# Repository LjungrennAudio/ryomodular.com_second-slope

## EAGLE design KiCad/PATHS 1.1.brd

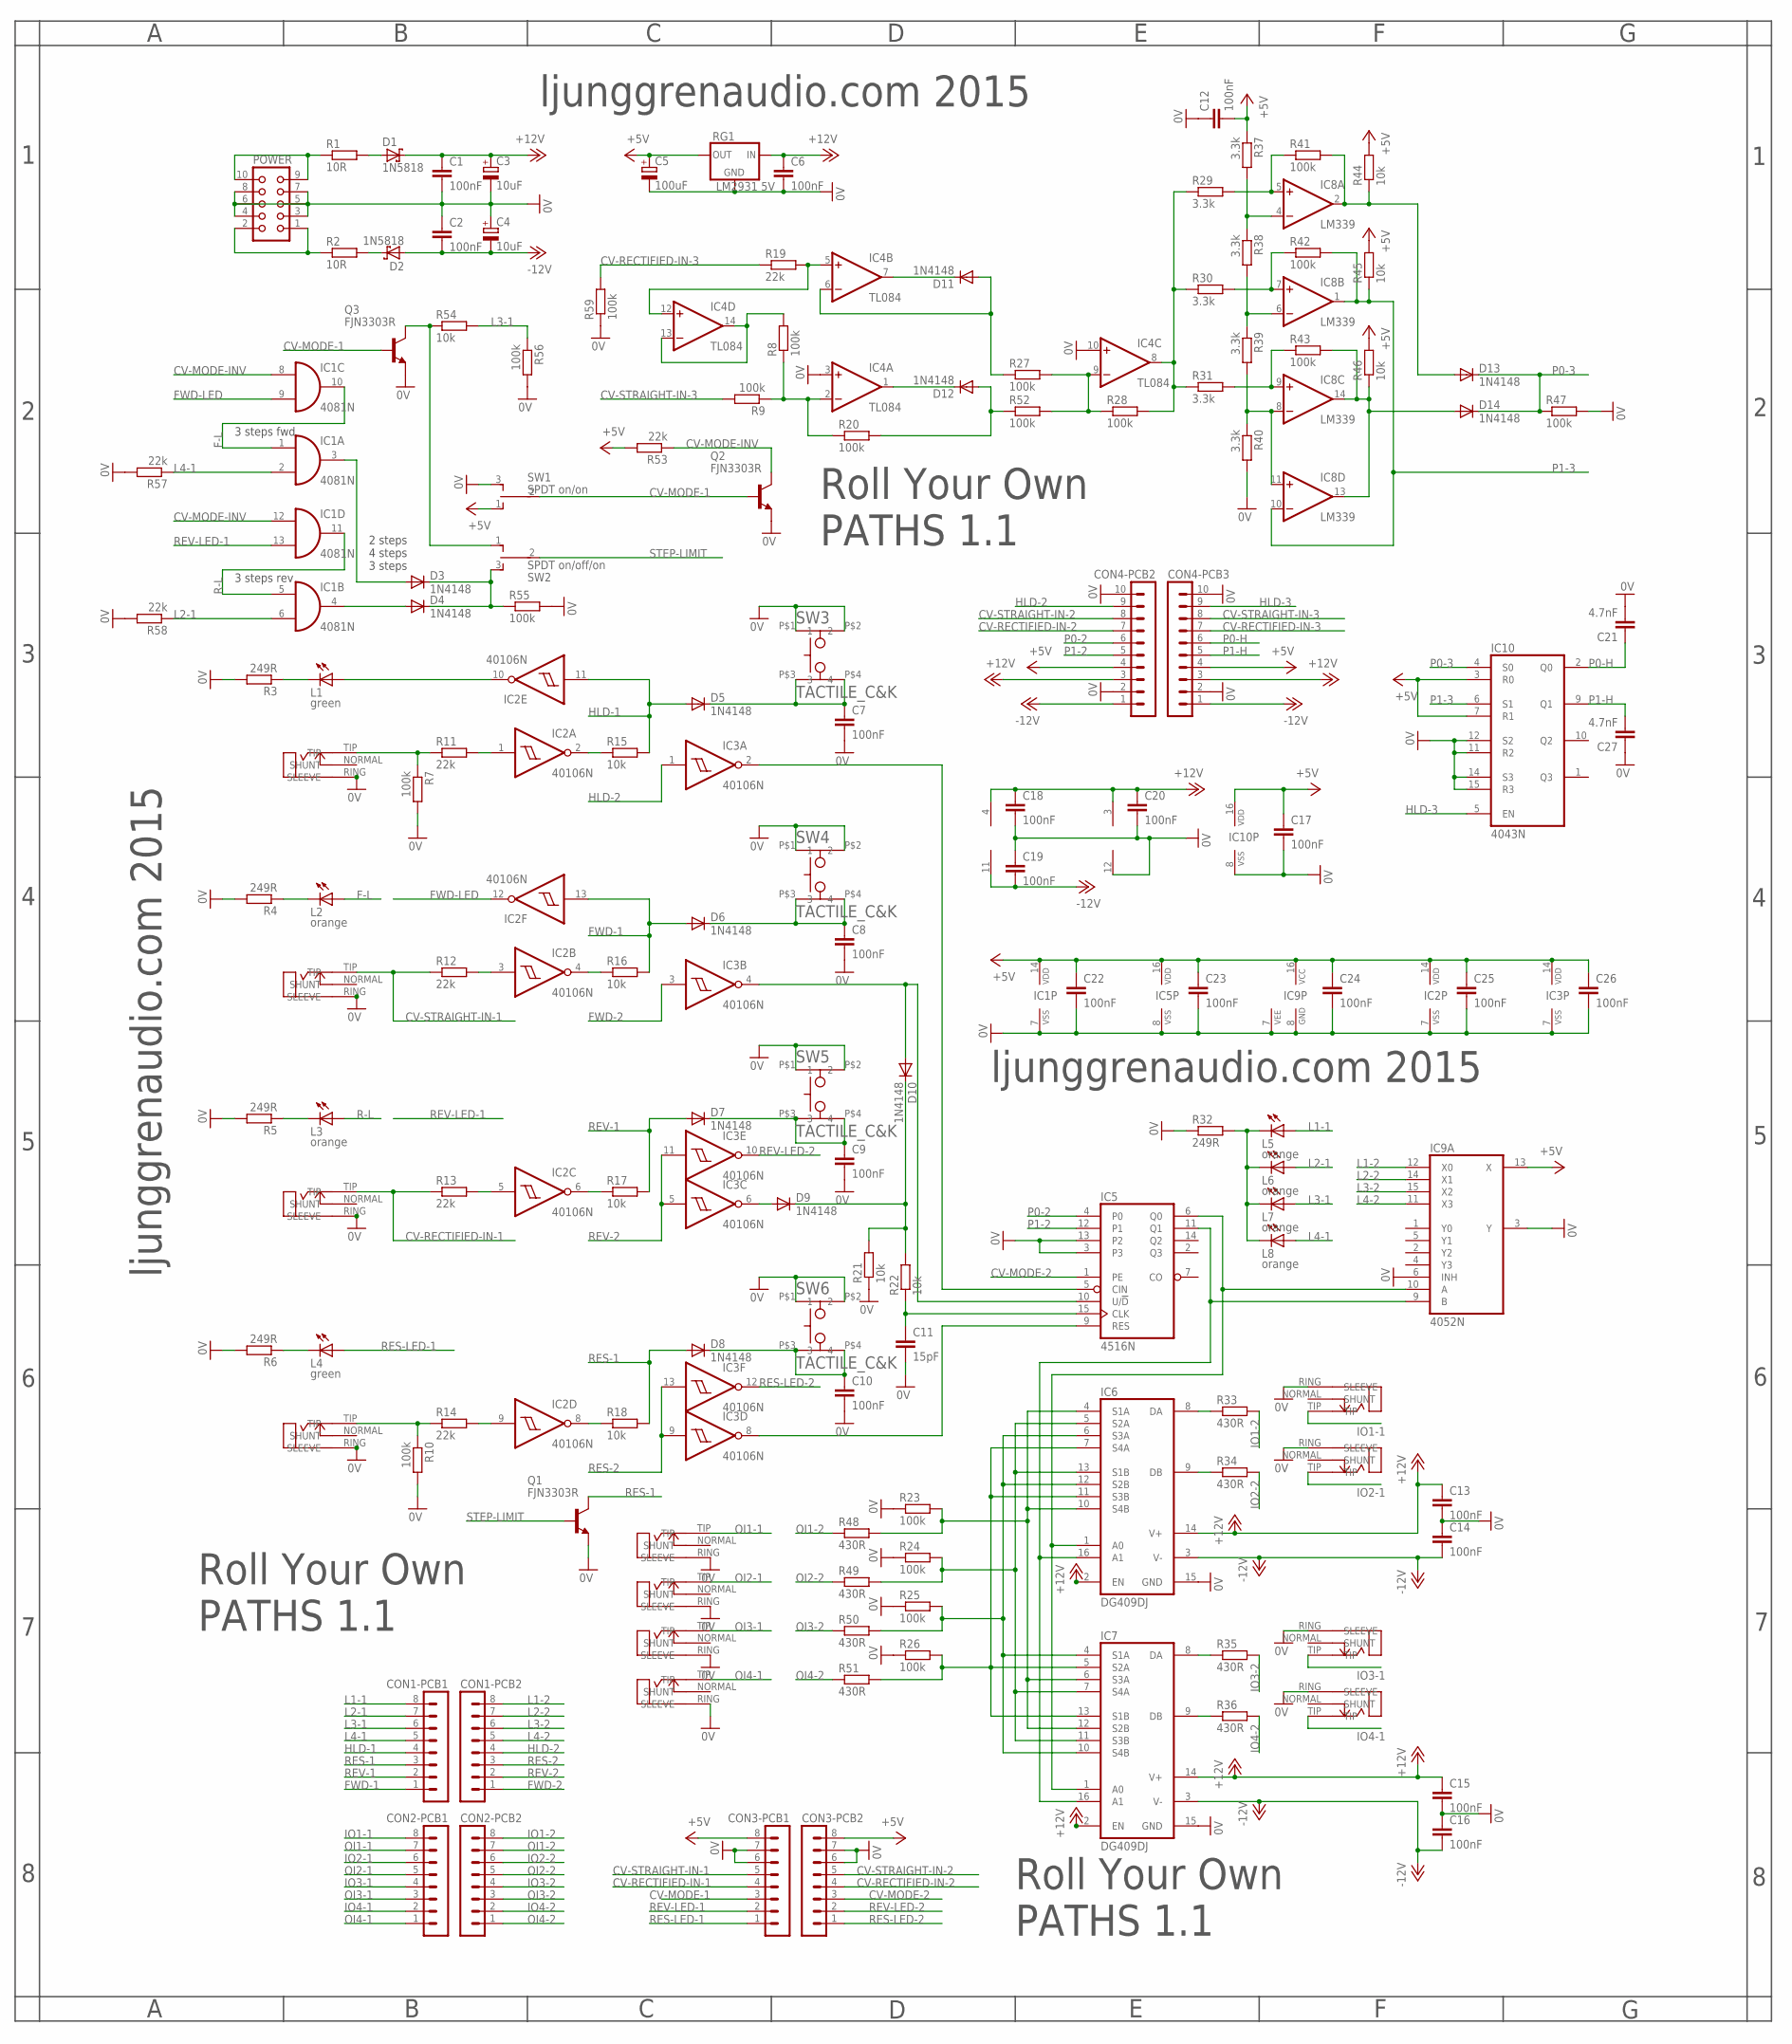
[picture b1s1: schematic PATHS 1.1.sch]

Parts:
C1, C2, C6, C7, C8, C9, C10, C12, C13, C14, C15, C16, C17, C18, C19, C20, C22, C23, C24, C25, C26: 100nF; C025-024X044
C3, C4: 10uF; E2-5
C5: 100uF; E2,5-6
C11: 15pF; C025-024X044
C21, C27: 4.7nF; C025-024X044
CON1-PCB1, CON1-PCB2, CON2-PCB1, CON2-PCB2, CON3-PCB1, CON3-PCB2: MA08-1
CON4-PCB2, CON4-PCB3: MA10-1
D1, D2: 1N5818; DO41-7
D3, D4, D5, D6, D7, D8, D9, D10, D11, D12, D13, D14: 1N4148; DO35-6
FWD: ERTHENVAR_3.5MM_JACKINLINE2; THONKICON-TWISTED
HLD: ERTHENVAR_3.5MM_JACKINLINE2; THONKICON-TWISTED
I/O1, I/O2, I/O3, I/O4: ERTHENVAR_3.5MM_JACKINLINE2; THONKICON-TWISTED
IC1: 4081N; DIL14
IC2, IC3: 40106N; DIL14
IC4: TL084; DIL14
IC5: 4516N; DIL16
IC6, IC7: DG409DJ; DIL16
IC8: LM339; DIL14
IC9: 4052N; DIL16
IC10: 4043N; DIL16
L1, L4: green; LED3MM
L2, L3, L5, L6, L7, L8: orange; LED3MM
O/I1, O/I2, O/I3, O/I4: ERTHENVAR_3.5MM_JACKINLINE2; THONKICON-TWISTED
POWER: CON10L
Q1, Q2, Q3: FJN3303R; TO92-LINE
R1, R2: 10R; 0207/9
R3, R4, R5, R6, R32: 249R; 0204/5
R7, R8, R9, R10, R20, R23, R24, R25, R26, R27, R28, R41, R42, R43, R47, R52, R55, R56, R59: 100k; 0204/5
R11, R12, R13, R14, R19, R53, R57, R58: 22k; 0204/5
R15, R16, R17, R18, R21, R22, R44, R45, R46, R54: 10k; 0204/5
R29, R30, R31, R37, R38, R39, R40: 3.3k; 0204/5
R33, R34, R35, R36, R48, R49, R50, R51: 430R; 0207/9
RES: ERTHENVAR_3.5MM_JACKINLINE2; THONKICON-TWISTED
REV: ERTHENVAR_3.5MM_JACKINLINE2; THONKICON-TWISTED
RG1: LM2931 5V; TO92-LINE
SW1: SPDT on/on; SPDT-HORIZONTAL-TOP-SUBMINI-MULTICOMP
SW2: SPDT on/off/on; SPDT-HORIZONTAL-TOP-SUBMINI-MULTICOMP
SW3, SW4, SW5, SW6: TACTILE_C&K; TACTILE_CK

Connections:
0V: C1.2, C2.1, C3.-, C4.+, C5.-, C6.2, C7.2, C8.2, C9.2, C10.2, C11.2, C12.1, C13.2, C14.1, C15.2, C16.1, C17.2, C18.2, C19.1, C20.2, C21.2, C22.2, C23.2, C24.2, C25.2, C26.2, C27.1, CON3-PCB1.6, CON3-PCB1.7, CON3-PCB2.6, CON3-PCB2.7, CON4-PCB2.2, CON4-PCB2.10, CON4-PCB3.2, CON4-PCB3.10, FWD.RING (SLEEVE), HLD.RING (SLEEVE), I/O1.RING (SLEEVE), I/O2.RING (SLEEVE), I/O3.RING (SLEEVE), I/O4.RING (SLEEVE), IC1.7 (VSS), IC2.7 (VSS), IC3.7 (VSS), IC4.3 (+IN), IC4.10 (+IN), IC5.3, IC5.8 (VSS), IC5.13 (P2), IC6.15 (GND), IC7.15 (GND), IC8.12 (V-), IC9.3 (Y), IC9.6 (INH), IC9.7 (VEE), IC9.8 (GND), IC10.8 (VSS), IC10.11 (R2), IC10.12 (S2), IC10.14 (S3), IC10.15 (R3), O/I1.RING (SLEEVE), O/I2.RING (SLEEVE), O/I3.RING (SLEEVE), O/I4.RING (SLEEVE), POWER.3, POWER.4, POWER.5, POWER.6, POWER.7, POWER.8, Q1.3 (E), Q2.3 (E), Q3.3 (E), R3.2, R4.2, R5.2, R6.2, R7.2, R10.2, R21.1, R23.1, R24.1, R25.1, R26.1, R32.1, R40.2, R47.2, R55.2, R56.2, R57.2, R58.2, R59.1, RES.RING (SLEEVE), REV.RING (SLEEVE), RG1.2 (GND), SW1.3, SW3.P$1 (1), SW3.P$2 (2), SW4.P$1 (1), SW4.P$2 (2), SW5.P$1 (1), SW5.P$2 (2), SW6.P$1 (1), SW6.P$2 (2)
+5V: C5.+, C12.2, C17.1, C22.1, C23.1, C24.1, C25.1, C26.1, CON3-PCB1.8, CON3-PCB2.8, CON4-PCB2.4, CON4-PCB3.4, IC1.14 (VDD), IC2.14 (VDD), IC3.14 (VDD), IC5.16 (VDD), IC9.13 (X), IC9.16 (VCC), IC10.3 (R0), IC10.7 (R1), IC10.16 (VDD), R37.1, R44.2, R45.2, R46.2, R53.2, RG1.3 (OUT), SW1.1
+12V: C1.1, C3.+, C6.1, C13.1, C15.1, C18.1, C20.1, CON4-PCB2.3, CON4-PCB3.3, D1.C, IC4.4 (V+), IC6.2 (EN), IC6.14 (V+), IC7.2 (EN), IC7.14 (V+), IC8.3 (V+), RG1.1 (IN)
-12V: C2.2, C4.-, C14.2, C16.2, C19.2, CON4-PCB2.1, CON4-PCB3.1, D2.A, IC4.11 (V-), IC6.3 (V-), IC7.3 (V-)
BDF3R2T: C9.1, D7.CATHODE (C), SW5.P$3 (3), SW5.P$4 (4)
CV-MODE-1: CON3-PCB1.3, Q2.1 (B), Q3.1 (B), SW1.2
CV-MODE-2: CON3-PCB2.3, IC5.1 (PE)
CV-MODE-INV: IC1.8 (I0), IC1.12 (I0), Q2.2 (C), R53.1
CV-RECTIFIED-IN-1: CON3-PCB1.4, R13.1, REV.TIP
CV-RECTIFIED-IN-2: CON3-PCB2.4, CON4-PCB2.7
CV-RECTIFIED-IN-3: CON4-PCB3.7, R19.1, R59.2
CV-STRAIGHT-IN-1: CON3-PCB1.5, FWD.TIP, R12.1
CV-STRAIGHT-IN-2: CON3-PCB2.5, CON4-PCB2.8
CV-STRAIGHT-IN-3: CON4-PCB3.8, R9.2
DFGT43: C8.1, D6.CATHODE (C), SW4.P$3 (3), SW4.P$4 (4)
DVW4D: D9.ANODE (A), IC3.6 (O)
F-L: IC1.1 (I0), IC1.10 (O), L2.A
FGDFS33: IC3.2 (O), IC5.5 (CIN)
FSS44F: IC3.8 (O), IC5.9 (RES)
FWD-1: CON1-PCB1.1, D6.ANODE (A), IC2.13 (I), R16.2
FWD-2: CON1-PCB2.1, IC3.3 (I)
FWD-LED: IC1.9 (I1), IC2.12 (O)
HLD-1: CON1-PCB1.4, D5.ANODE (A), IC2.11 (I), R15.2
HLD-2: CON1-PCB2.4, CON4-PCB2.9, IC3.1 (I)
HLD-3: CON4-PCB3.9, IC10.5 (EN)
IO1-1: CON2-PCB1.8, I/O1.TIP
IO1-2: CON2-PCB2.8, R33.2
IO2-1: CON2-PCB1.6, I/O2.TIP
IO2-2: CON2-PCB2.6, R34.2
IO3-1: CON2-PCB1.4, I/O3.TIP
IO3-2: CON2-PCB2.4, R35.2
IO4-1: CON2-PCB1.2, I/O4.TIP
IO4-2: CON2-PCB2.2, R36.2
L1-1: CON1-PCB1.8, L5.A
L1-2: CON1-PCB2.8, IC9.12 (X0)
L2-1: CON1-PCB1.7, IC1.6 (I1), L6.A, R58.1
L2-2: CON1-PCB2.7, IC9.14 (X1)
L3-1: CON1-PCB1.6, L7.A, R54.2, R56.1
L3-2: CON1-PCB2.6, IC9.15 (X2)
L4-1: CON1-PCB1.5, IC1.2 (I1), L8.A, R57.1
L4-2: CON1-PCB2.5, IC9.11 (X3)
unnamed: IC5.11 (Q1), IC6.16 (A1), IC7.16 (A1), IC9.9 (B)
unnamed: IC5.6 (Q0), IC6.1 (A0), IC7.1 (A0), IC9.10 (A)
unnamed: IC2.3 (I), R12.2
unnamed: C11.1, IC5.15 (CLK), R22.1
unnamed: IC6.9 (DB), R34.1
unnamed: IC7.9 (DB), R36.1
unnamed: L2.K (C), R4.1
unnamed: HLD.TIP, R7.1, R11.1
unnamed: IC7.8 (DA), R35.1
unnamed: IC2.4 (O), R16.1
unnamed: IC2.6 (O), R17.1
unnamed: R10.1, R14.1, RES.TIP
unnamed: IC6.8 (DA), R33.1
unnamed: L1.K (C), R3.1
unnamed: L3.K (C), R5.1
unnamed: IC2.8 (O), R18.1
unnamed: C10.1, D8.CATHODE (C), SW6.P$3 (3), SW6.P$4 (4)
unnamed: IC2.10 (O), L1.A
unnamed: D3.ANODE (A), IC1.3 (O)
unnamed: L4.K (C), R6.1
unnamed: IC2.5 (I), R13.2
unnamed: POWER.1, POWER.2, R2.1
unnamed: POWER.9, POWER.10, R1.1
unnamed: D1.A, R1.2
unnamed: D2.C, R2.2
unnamed: IC2.9 (I), R14.2
unnamed: IC2.2 (O), R15.1
unnamed: C7.1, D5.CATHODE (C), SW3.P$3 (3), SW3.P$4 (4)
unnamed: IC4.2 (-IN), R8.1, R9.1, R20.1
unnamed: D4.ANODE (A), IC1.4 (O)
unnamed: IC8.4 (-IN), R37.2, R38.1
unnamed: IC8.6 (-IN), R38.2, R39.1
unnamed: IC8.8 (-IN), IC8.11 (+IN), R39.2, R40.1
unnamed: D11.ANODE (A), IC4.6 (-IN), R27.1
unnamed: IC8.9 (+IN), R31.2, R43.1
unnamed: IC8.7 (+IN), R30.2, R42.1
unnamed: IC8.5 (+IN), R29.2, R41.1
unnamed: D9.CATHODE (C), D10.CATHODE (C), R21.2, R22.2
unnamed: L5.K (C), L6.K (C), L7.K (C), L8.K (C), R32.2
unnamed: D14.ANODE (A), IC8.13 (OUT), IC8.14 (OUT), R43.2, R46.1
unnamed: IC6.6 (S3A), IC6.12 (S2B), IC7.4 (S1A), IC7.10 (S4B), R25.2, R50.2
unnamed: D13.ANODE (A), IC8.2 (OUT), R41.2, R44.1
unnamed: IC4.5 (+IN), IC4.12 (+IN), R19.2
unnamed: D11.CATHODE (C), IC4.7 (OUT)
unnamed: D3.CATHODE (C), D4.CATHODE (C), R55.1, SW2.3
unnamed: IC6.7 (S4A), IC6.11 (S3B), IC7.5 (S2A), IC7.13 (S1B), R26.2, R51.2
unnamed: IC2.1 (I), R11.2
unnamed: D12.CATHODE (C), IC4.1 (OUT)
unnamed: IC4.9 (-IN), R27.2, R28.1, R52.2
unnamed: IC4.8 (OUT), R28.2, R29.1, R30.1, R31.1
unnamed: IC6.5 (S2A), IC6.13 (S1B), IC7.7 (S4A), IC7.11 (S3B), R24.2, R49.2
unnamed: IC6.4 (S1A), IC6.10 (S4B), IC7.6 (S3A), IC7.12 (S2B), R23.2, R48.2
unnamed: IC4.13 (-IN), IC4.14 (OUT), R8.2
unnamed: D12.ANODE (A), R20.2, R52.1
unnamed: Q3.2 (C), R54.1, SW2.1
OI1-1: CON2-PCB1.7, O/I1.TIP
OI1-2: CON2-PCB2.7, R48.1
OI2-1: CON2-PCB1.5, O/I2.TIP
OI2-2: CON2-PCB2.5, R49.1
OI3-1: CON2-PCB1.3, O/I3.TIP
OI3-2: CON2-PCB2.3, R50.1
OI4-1: CON2-PCB1.1, O/I4.TIP
OI4-2: CON2-PCB2.1, R51.1
P0-2: CON4-PCB2.6, IC5.4 (P0)
P0-3: D13.CATHODE (C), D14.CATHODE (C), IC10.4 (S0), R47.1
P0-H: C21.1, CON4-PCB3.6, IC10.2 (Q0)
P1-2: CON4-PCB2.5, IC5.12 (P1)
P1-3: IC8.1 (OUT), IC8.10 (-IN), IC10.6 (S1), R42.2, R45.1
P1-H: C27.2, CON4-PCB3.5, IC10.9 (Q1)
R-L: IC1.5 (I0), IC1.11 (O), L3.A
RES-1: CON1-PCB1.3, D8.ANODE (A), Q1.2 (C), R18.2
RES-2: CON1-PCB2.3, IC3.9 (I), IC3.13 (I)
RES-LED-1: CON3-PCB1.1, L4.A
RES-LED-2: CON3-PCB2.1, IC3.12 (O)
REV-1: CON1-PCB1.2, D7.ANODE (A), R17.2
REV-2: CON1-PCB2.2, IC3.5 (I), IC3.11 (I)
REV-LED-1: CON3-PCB1.2, IC1.13 (I1)
REV-LED-2: CON3-PCB2.2, IC3.10 (O)
STEP-LIMIT: Q1.1 (B), SW2.2
XBGE4: D10.ANODE (A), IC3.4 (O), IC5.10 (U/!D)

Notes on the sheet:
2 steps 4 steps 3 steps
3 steps fwd
3 steps rev
Roll Your Own PATHS 1.1
ljunggrenaudio.com 2015

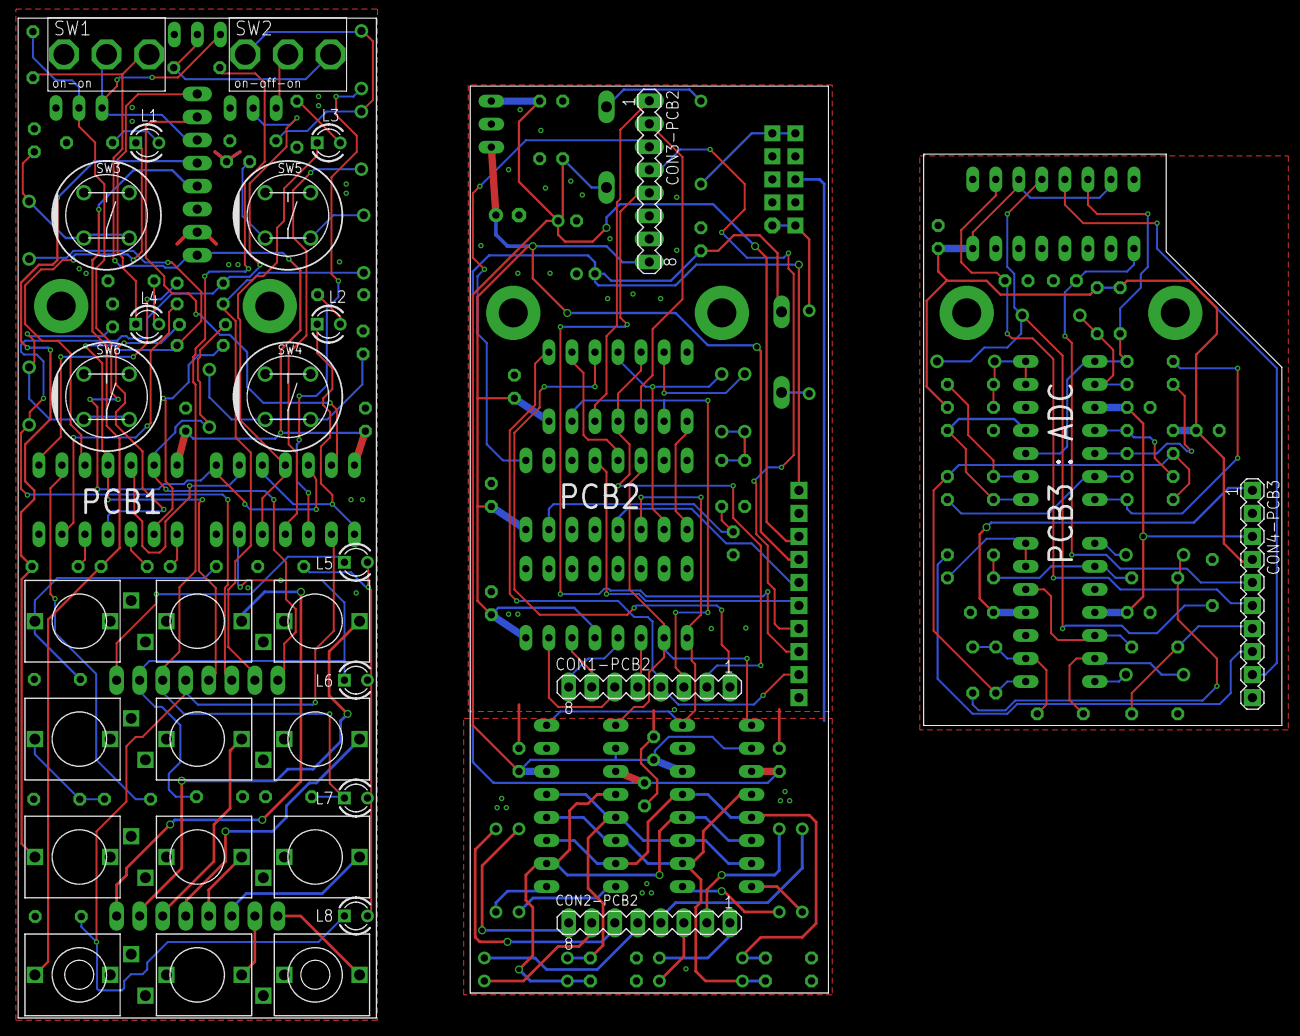
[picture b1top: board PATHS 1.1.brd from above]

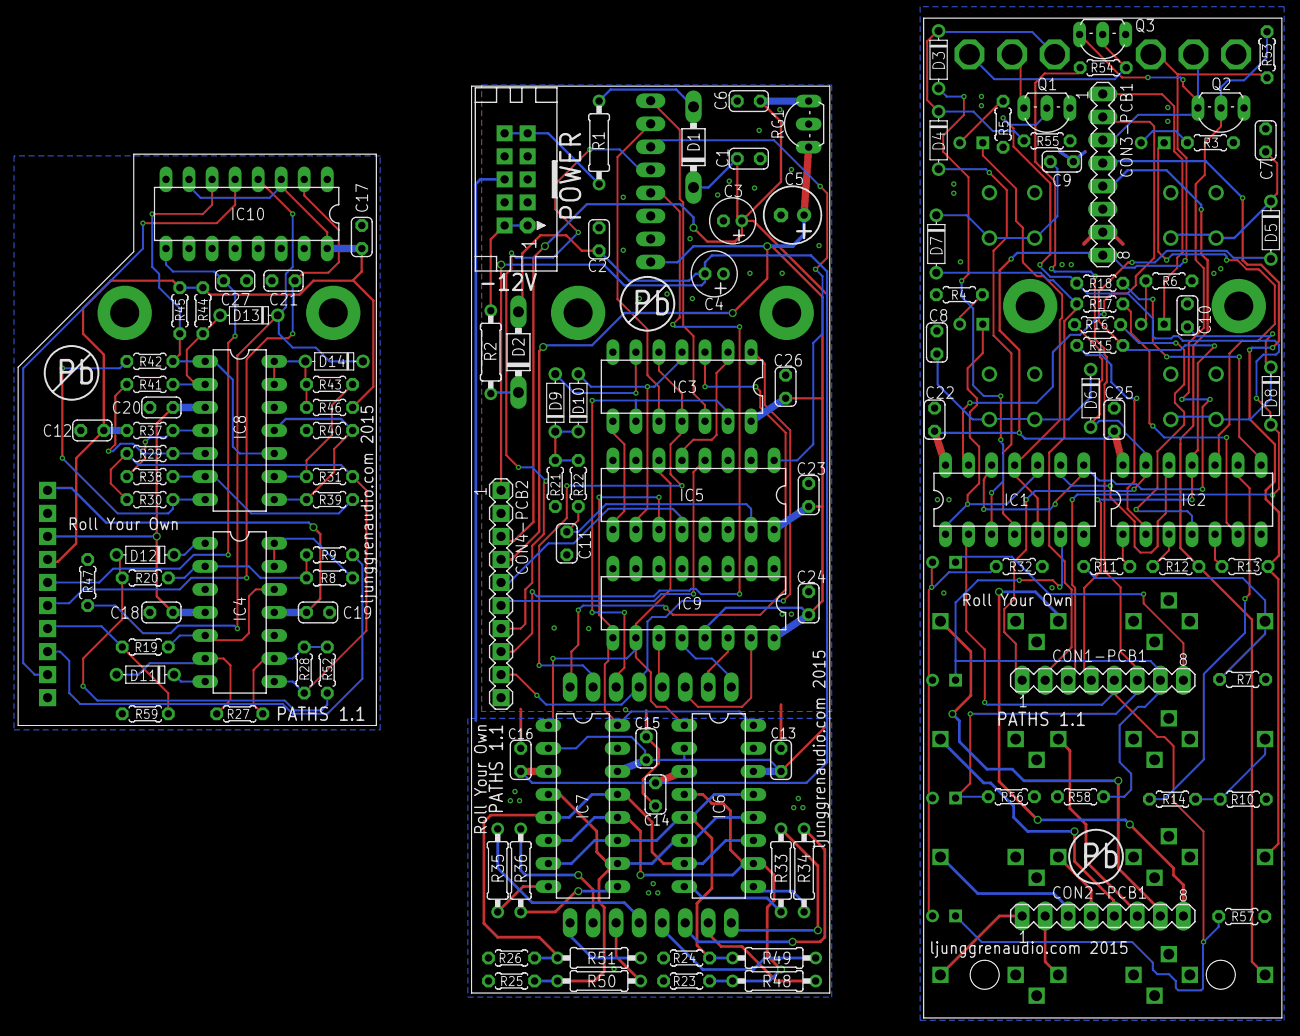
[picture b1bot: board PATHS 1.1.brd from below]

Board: 2 copper layers, 139.3 x 110.2 mm, 149 parts (119 on the bottom side), 121 nets.

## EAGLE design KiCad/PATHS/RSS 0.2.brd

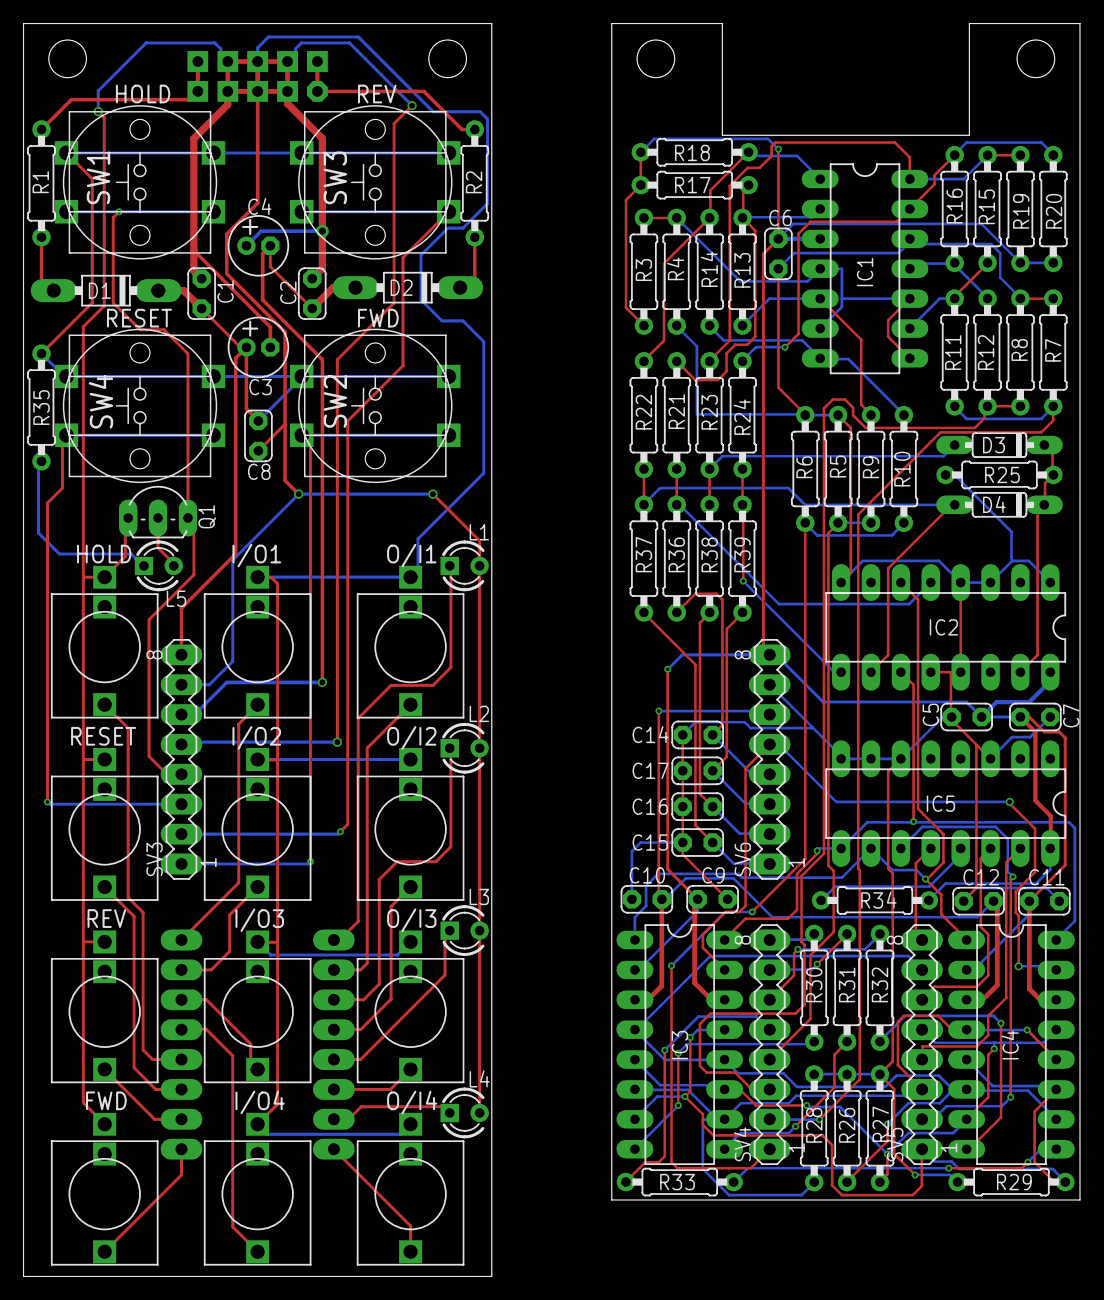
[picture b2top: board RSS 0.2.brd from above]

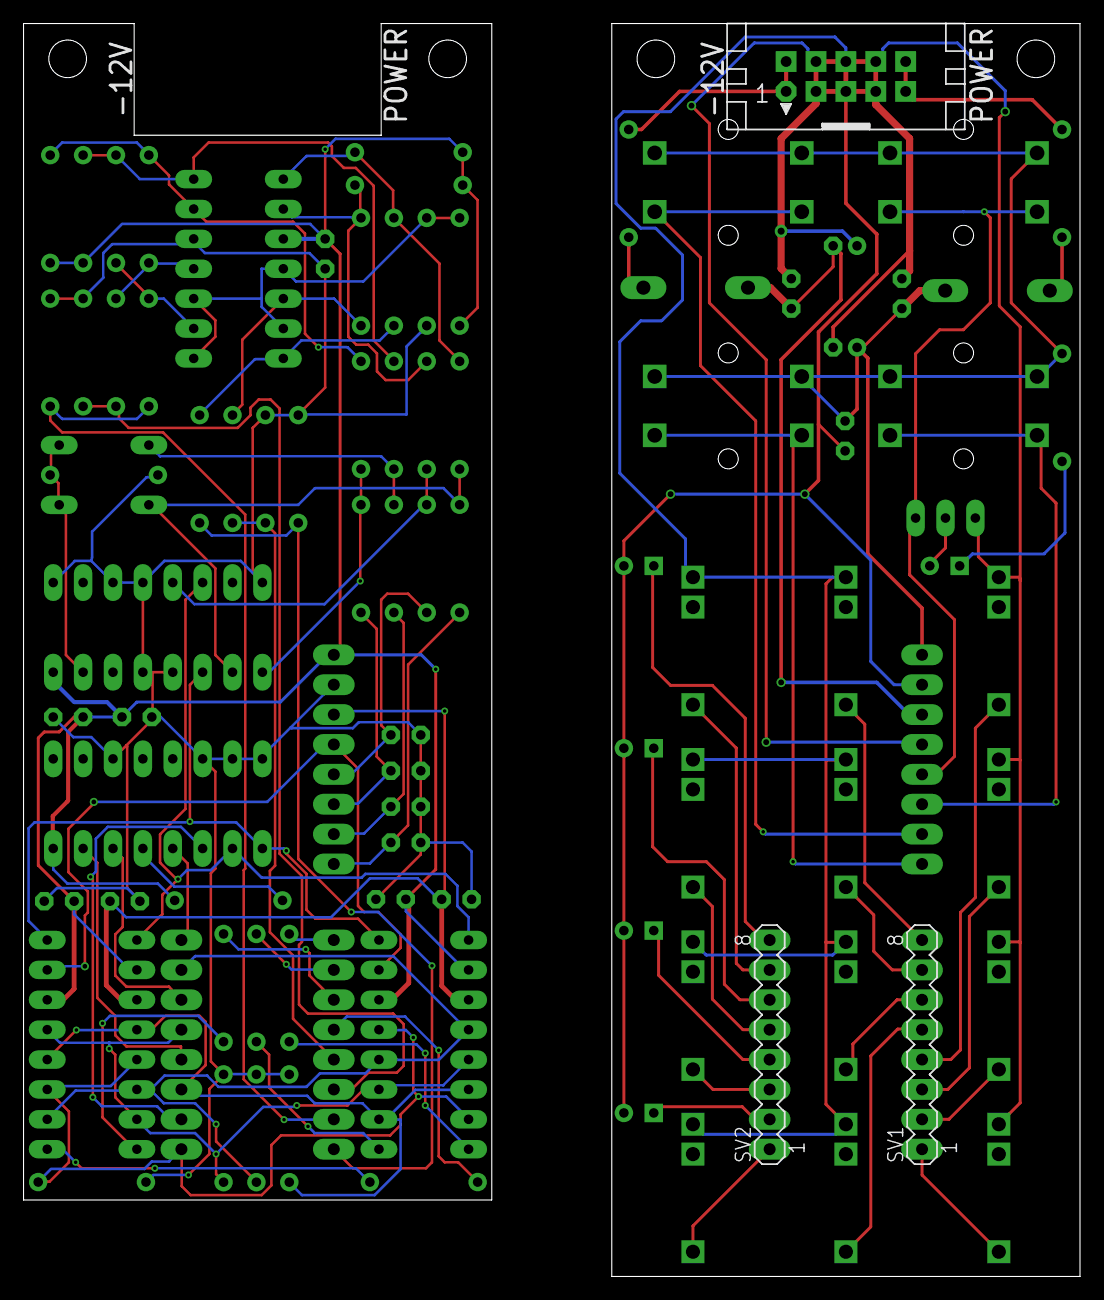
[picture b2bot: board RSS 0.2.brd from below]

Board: 2 copper layers, 89.8 x 106.5 mm, 93 parts (3 on the bottom side), 71 nets.

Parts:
C1, C2, C5, C6, C7, C8, C9, C10, C11, C12, C14, C15, C16, C17: 100nF; C025-024X044
C3, C4: 10uF; E2-5
D1, D2: 1N5818; DO41-7
D3, D4: 1N4148; DO35-7
FWD: ERTHENVAR_3.5MM_JACK; THONKICON
HLD: ERTHENVAR_3.5MM_JACK; THONKICON
I/O1, I/O2, I/O3, I/O4: ERTHENVAR_3.5MM_JACK; THONKICON
IC1: LM339; DIL14
IC2: 4516N; DIL16
IC3, IC4: DG409DJ; DIL16
IC5: 4052N; DIL16
L1, L2, L3, L4: orange; LED3MM
L5: green; LED3MM
O/I1, O/I2, O/I3, O/I4: ERTHENVAR_3.5MM_JACK; THONKICON
POWER: CON10L
Q1: FJN3303R; TO92-LINE
R1, R2: 10R; 0207/9
R3, R5, R6, R7, R8, R13, R14, R15, R16, R25, R26, R27, R28, R29: 100k; 0207/9
R4, R17, R18, R19, R20, R21, R22, R23, R24: 22k; 0207/9
R9, R10, R11, R12: 2.2k; 0207/9
R30, R31, R32, R33, R36, R37, R38, R39: 1k; 0207/9
R34, R35: 1.8k; 0207/9
RES: ERTHENVAR_3.5MM_JACK; THONKICON
REV: ERTHENVAR_3.5MM_JACK; THONKICON
SV1, SV2, SV3, SV4, SV5, SV6: MA08-1
SW1: HLD; TACTILE_ALPS
SW2: FWD; TACTILE_ALPS
SW3: REV; TACTILE_ALPS
SW4: RES; TACTILE_ALPS

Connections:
0V: C1.2, C2.1, C3.-, C4.+, C5.2, C6.2, C7.2, C8.2, C9.2, C10.1, C11.2, C12.1, C14.2, C15.2, C16.2, C17.2, FWD.RING, HLD.RING, I/O1.RING, I/O2.RING, I/O3.RING, I/O4.RING, IC1.12, IC2.1, IC2.3, IC2.4, IC2.8, IC2.12, IC2.13, IC5.3, IC5.6, IC5.7, IC5.8, L1.K, L2.K, L3.K, L4.K, O/I1.RING, O/I2.RING, O/I3.RING, O/I4.RING, POWER.3, POWER.4, POWER.5, POWER.6, POWER.7, POWER.8, Q1.3, R4.1, R5.2, R6.2, R7.2, R8.2, R25.1, R26.1, R27.1, R28.1, R29.1, RES.RING, REV.RING, SV3.5, SV3.7, SV6.7
+12V: C1.1, C3.+, C5.1, C6.1, C7.1, C8.1, C9.1, C11.1, D1.C, IC1.3, IC2.16, IC3.2, IC3.14, IC4.2, IC4.14, IC5.16, R3.1, R17.2, R18.2, R19.2, R20.2, R34.2, R35.2, SV3.8, SV6.8, SW1.1, SW1.2, SW2.1, SW2.2, SW3.1, SW3.2, SW4.1, SW4.2
-12V: C2.2, C4.-, C10.2, C12.2, D2.A, IC3.3, IC4.3, SV3.6, SV6.6
FWD-1: FWD.TIP, SV1.1
FWD-2: R6.1, R10.1, SV4.1
HLD-1: HLD.TIP, SV1.4
HLD-2: R5.1, R9.1, SV4.4
IO1-1: I/O1.TIP, SV1.8
IO1-2: R30.2, SV4.8
IO2-1: I/O2.TIP, SV1.7
IO2-2: R31.2, SV4.7
IO3-1: I/O3.TIP, SV1.6
IO3-2: R32.2, SV4.6
IO4-1: I/O4.TIP, SV1.5
IO4-2: R33.2, SV4.5
L1-1: L1.A, SV2.8
L1-2: IC5.12, SV5.8
L2-1: L2.A, SV2.6
L2-2: IC5.14, SV5.6
L3-1: L3.A, SV2.4
L3-2: IC5.15, SV5.4
L4-1: L4.A, SV2.2
L4-2: IC5.11, SV5.2
unnamed: IC2.11, IC3.16, IC4.16, IC5.9
unnamed: IC2.6, IC3.1, IC4.1, IC5.10
unnamed: IC3.15, IC4.15, SV6.5
unnamed: IC4.9, R33.1
unnamed: IC4.8, R32.1
unnamed: IC3.9, R31.1
unnamed: IC3.8, R30.1
unnamed: IC1.14, R15.2, R19.1, R23.1
unnamed: IC5.13, R34.1
unnamed: IC2.5, R21.2, R36.1
unnamed: IC1.7, R10.2, R14.1
unnamed: POWER.1, POWER.2, R2.1
unnamed: POWER.9, POWER.10, R1.1
unnamed: D1.A, R1.2
unnamed: D2.C, R2.2
unnamed: IC1.5, R9.2, R13.1
unnamed: IC1.9, R11.2, R15.1
unnamed: IC1.2, R13.2, R17.1, R21.1
unnamed: IC1.4, IC1.6, IC1.8, IC1.10, R3.2, R4.2
unnamed: IC1.11, R12.2, R16.1
unnamed: D4.A, IC2.10, R22.2, R37.1
unnamed: IC2.9, R24.2, R39.1
unnamed: D3.C, D4.C, IC2.15, R25.2
unnamed: IC1.13, R16.2, R20.1, R24.1
unnamed: L5.A, R35.1
unnamed: IC1.1, R14.2, R18.1, R22.1
unnamed: L5.K, Q1.2
unnamed: D3.A, R23.2, R38.1
OI1-1: O/I1.TIP, SV2.7
OI1-2: IC3.4, IC3.12, IC4.6, IC4.10, R26.2, SV5.7
OI2-1: O/I2.TIP, SV2.5
OI2-2: IC3.5, IC3.11, IC4.7, IC4.13, R27.2, SV5.5
OI3-1: O/I3.TIP, SV2.3
OI3-2: IC3.6, IC3.10, IC4.4, IC4.12, R28.2, SV5.3
OI4-1: O/I4.TIP, SV2.1
OI4-2: IC3.7, IC3.13, IC4.5, IC4.11, R29.2, SV5.1
RES-1: RES.TIP, SV1.3
RES-2: R8.1, R12.1, SV4.3
REV-1: REV.TIP, SV1.2
REV-2: R7.1, R11.1, SV4.2
SW1-1: Q1.1, SV3.4, SW1.3, SW1.4
SW1-2: C14.1, R36.2, SV6.4
SW2-1: SV3.1, SW2.3, SW2.4
SW2-2: C15.1, R37.2, SV6.1
SW3-1: SV3.2, SW3.3, SW3.4
SW3-2: C16.1, R38.2, SV6.2
SW4-1: SV3.3, SW4.3, SW4.4
SW4-2: C17.1, R39.2, SV6.3
